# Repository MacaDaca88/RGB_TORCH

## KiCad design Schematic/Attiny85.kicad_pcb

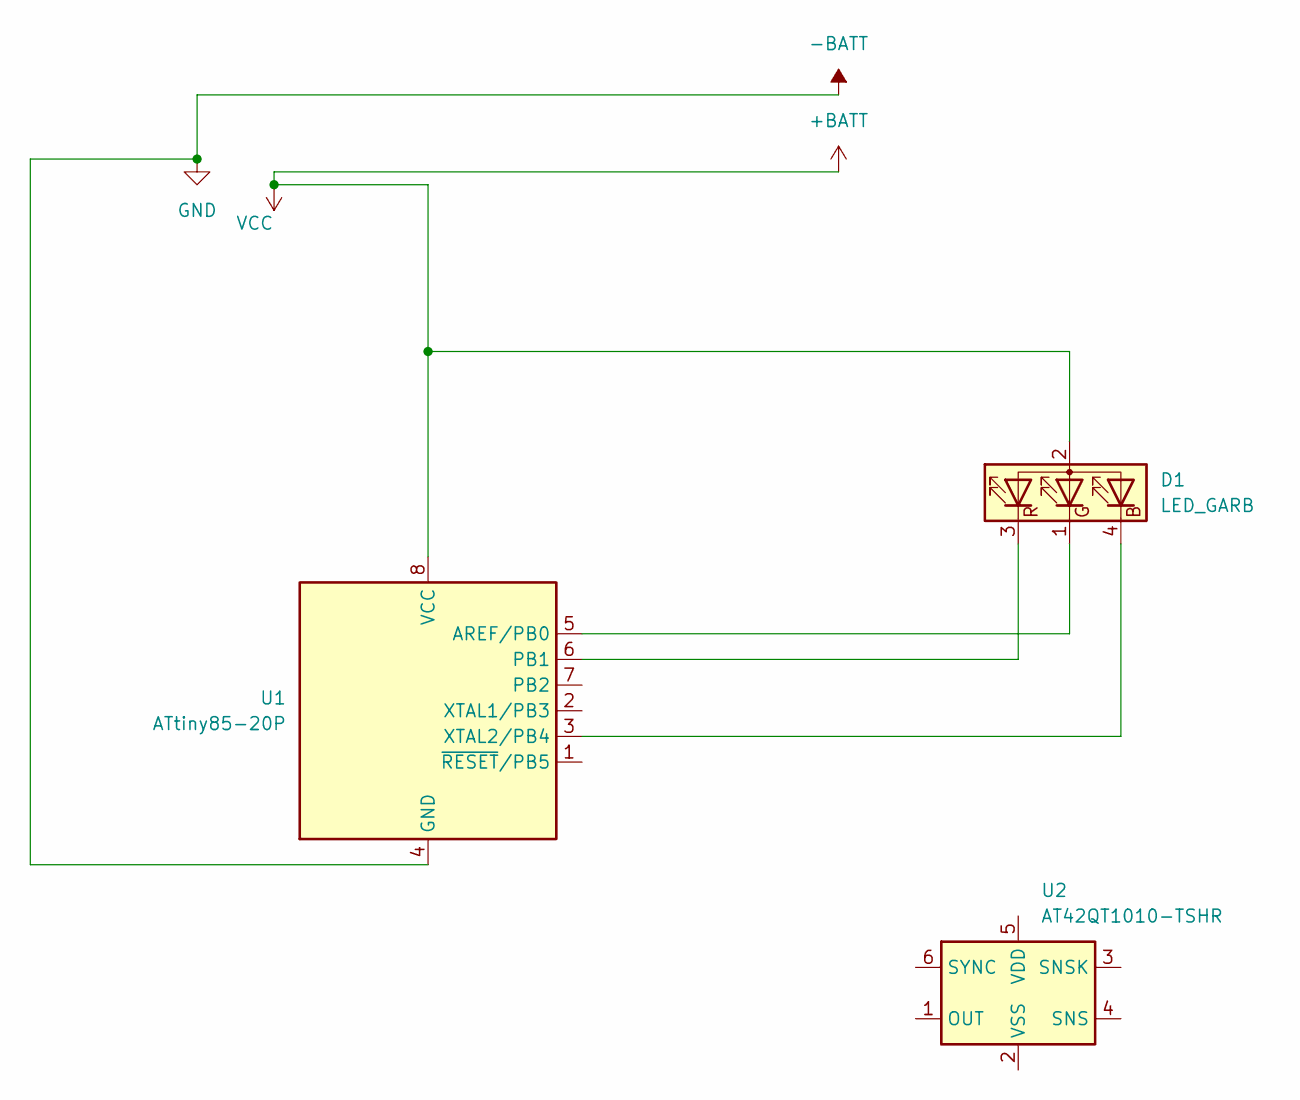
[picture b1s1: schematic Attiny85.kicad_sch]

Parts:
D1: LED_GARB; LED_BL-FL7680RGB
U1: ATtiny85-20P; DIP-8_W7.62mm
U2: AT42QT1010-TSHR; SOT-23-6

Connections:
+BATT: D1.2 (A), U1.8 (VCC)
-BATT: U1.4 (GND)
unnamed: D1.4 (BK), U1.3 (XTAL2/PB4)
unnamed: D1.1 (GK), U1.5 (AREF/PB0)
unnamed: D1.3 (RK), U1.6 (PB1)

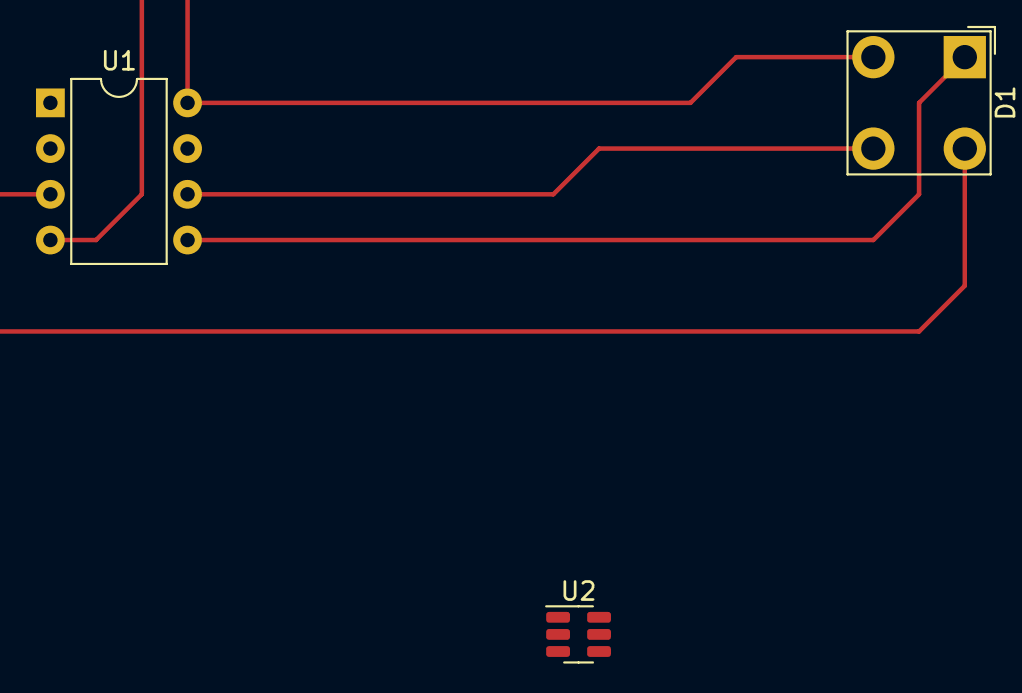
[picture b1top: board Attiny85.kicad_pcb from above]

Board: 2 copper layers, 3 parts (0 on the bottom side), 4 nets.

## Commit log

2023-11-09 Sorted
